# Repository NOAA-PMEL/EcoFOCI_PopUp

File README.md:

# EcoFOCI_PopUp

Under Ice 'Pop-Up' Buoy

################

Legal Disclaimer

This repository is a software product and is not official communication of the National Oceanic and Atmospheric Administration (NOAA), or the United States Department of Commerce (DOC). All NOAA GitHub project code is provided on an 'as is' basis and the user assumes responsibility for its use. Any claims against the DOC or DOC bureaus stemming from the use of this GitHub project will be governed by all applicable Federal law. Any reference to specific commercial products, processes, or services by service mark, trademark, manufacturer, or otherwise, does not constitute or imply their endorsement, recommendation, or favoring by the DOC. The DOC seal and logo, or the seal and logo of a DOC bureau, shall not be used in any manner to imply endorsement of any commercial product or activity by the DOC or the United States Government.

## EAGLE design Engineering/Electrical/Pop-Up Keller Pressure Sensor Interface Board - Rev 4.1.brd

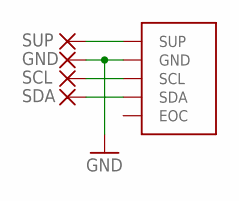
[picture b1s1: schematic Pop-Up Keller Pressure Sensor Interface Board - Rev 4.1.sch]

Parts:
GND: SMD075X015; SMD-0,75X0,15
P1: 4LD; KELLER-4-LD
SCL: SMD075X015; SMD-0,75X0,15
SDA: SMD075X015; SMD-0,75X0,15
SUP: SMD075X015; SMD-0,75X0,15

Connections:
GND: GND.P$1, P1.GND
unnamed: P1.SUP, SUP.P$1
unnamed: P1.SCL, SCL.P$1
unnamed: P1.SDA, SDA.P$1

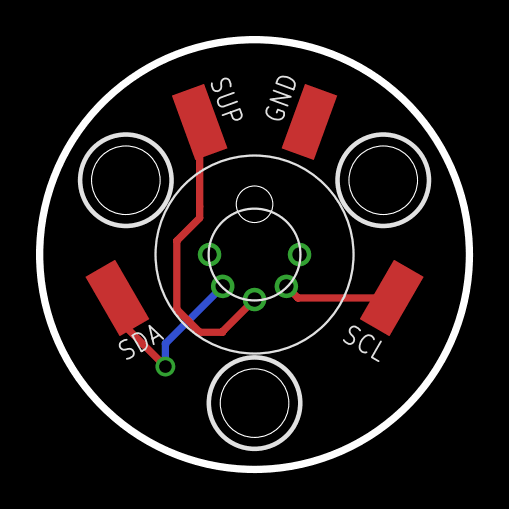
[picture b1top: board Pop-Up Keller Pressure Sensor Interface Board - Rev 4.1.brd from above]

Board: 2 copper layers, 23.9 x 23.9 mm, 5 parts (0 on the bottom side), 4 nets.

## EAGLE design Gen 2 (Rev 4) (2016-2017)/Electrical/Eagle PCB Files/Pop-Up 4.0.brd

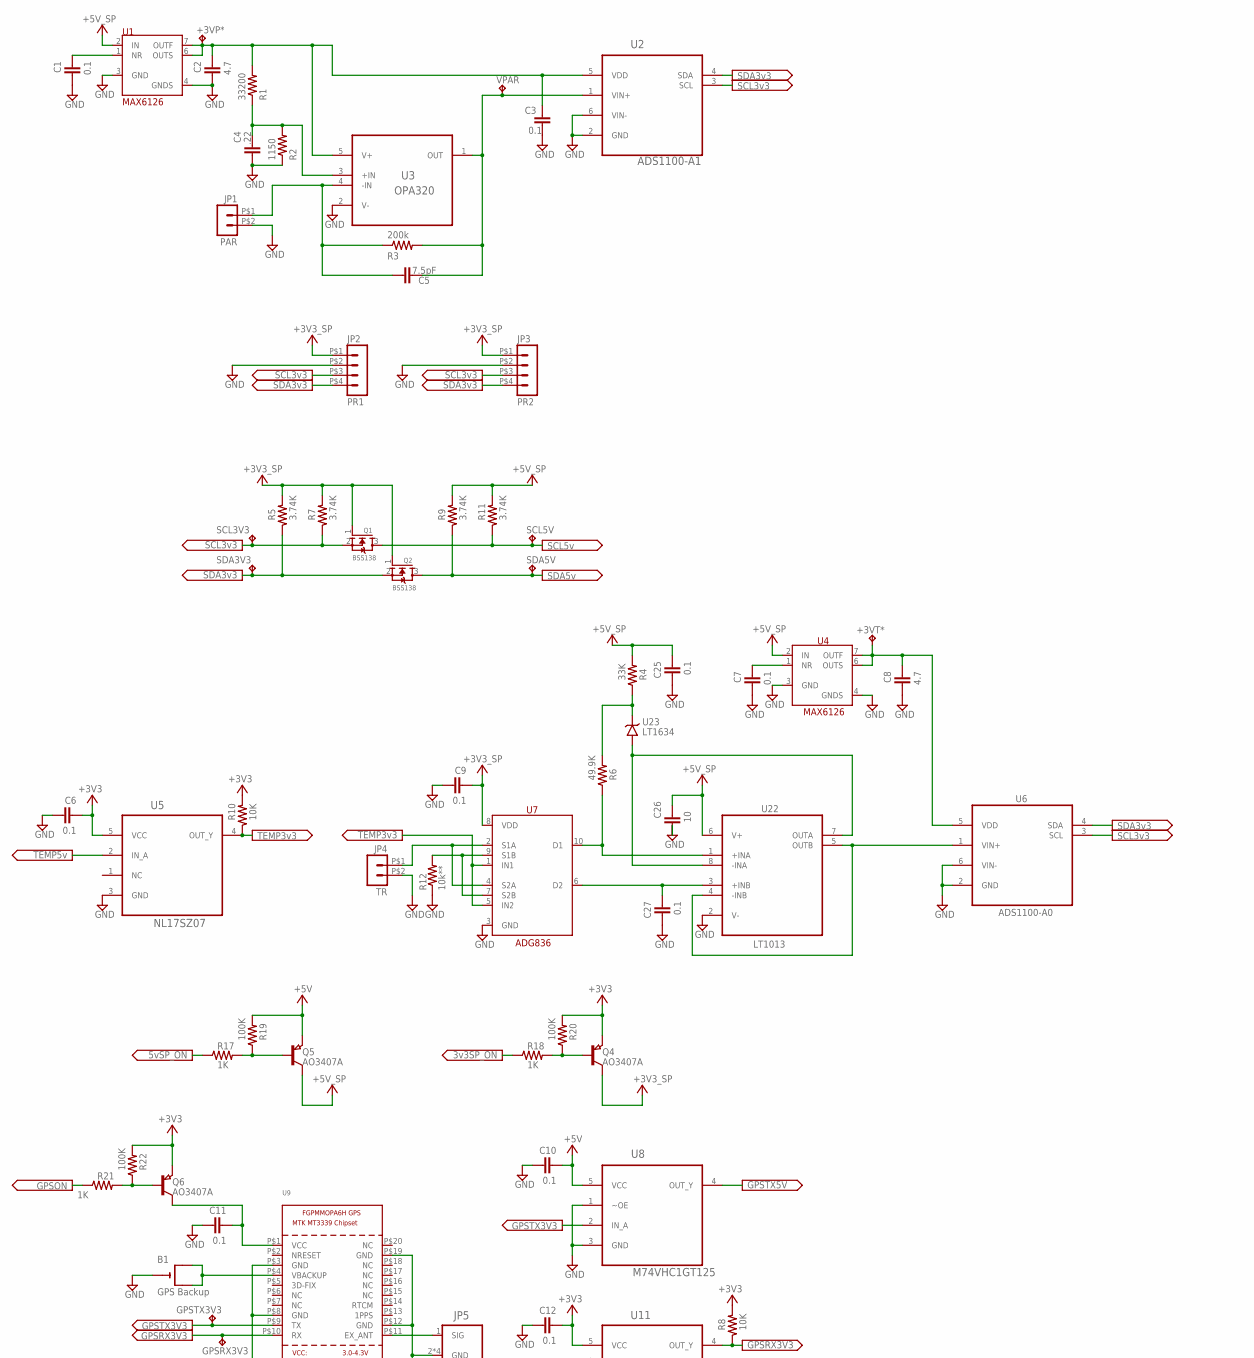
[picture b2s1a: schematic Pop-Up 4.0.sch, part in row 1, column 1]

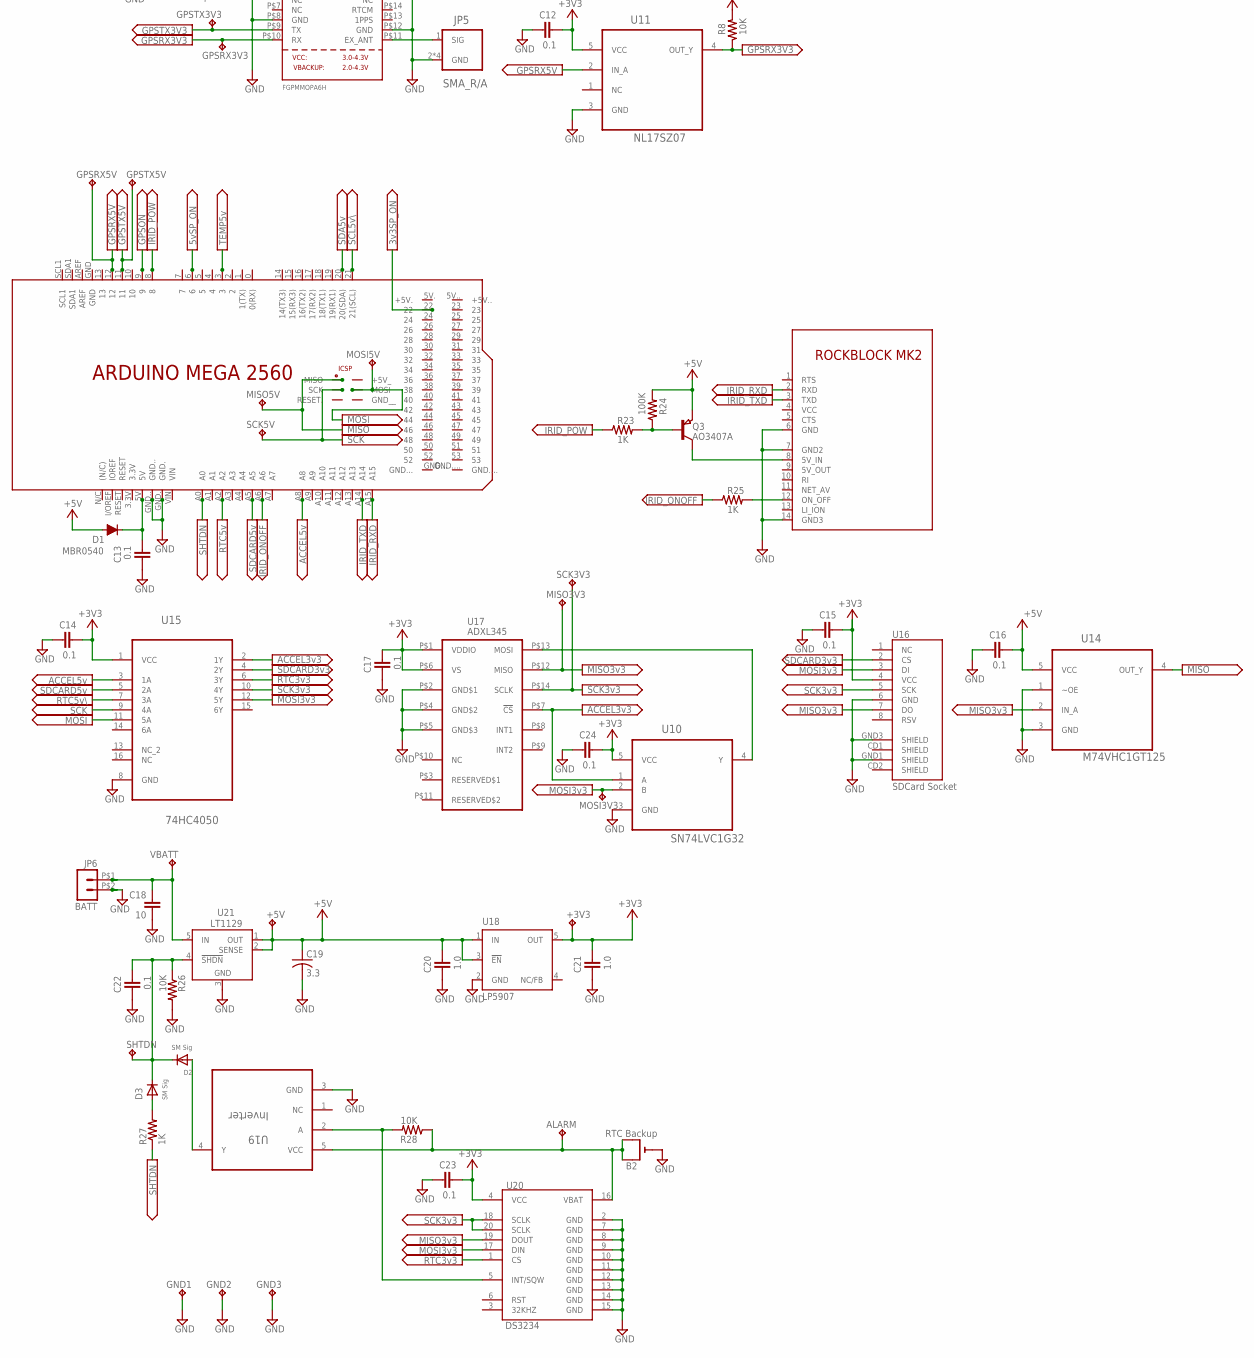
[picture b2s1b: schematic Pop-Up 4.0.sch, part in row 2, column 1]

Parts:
+3V3, +3VP*, +3VT*, +5V: TP-040
ALARM: TP-040
B1: GPS Backup; CR1220-SMD
B2: RTC Backup; CR1220-SMD
C1, C3, C6, C7, C9, C10, C11, C12, C13, C14, C15, C16, C17, C22, C23, C24, C25, C27: 0.1; 0603-CAP; MPN 2222 370 21104
C2, C8: 4.7; 0603-CAP; MPN 2222 370 21104
C4: .22; 0603-CAP; MPN 2222 370 21104
C5: 7.5pF; 0603-CAP; MPN 2222 370 21104
C18: 10; C1206
C19: 3.3; C1206
C20, C21: 1.0; 0603-CAP; MPN 2222 370 21104
C26: 10; C1206; MPN 2222 370 21104
D1: MBR0540; SOD123
D2, D3: SM Sig; SOD-323F
GND1, GND2, GND3: TP-040
GPSRX3V3, GPSRX5V: TP-040
GPSTX3V3, GPSTX5V: TP-040
JP1: PAR; 43650-0215
JP2: PR1; 43650-0415
JP3: PR2; 43650-0415
JP4: TR; 43650-0215
JP5: SMA_R/A; AMPHENOL_901-143
JP6: BATT; 43650-0215
MISO3V3, MISO5V: TP-040
MOSI3V3, MOSI5V: TP-040
Q1, Q2: BSS138; SOT23
Q3, Q4, Q5, Q6: AO3407A; SOT23
R1: 33200; R0603
R2: 1150; R0603
R3: 200k; R0603
R4: 33K; R0603
R5, R7, R9, R11: 3.74K; R0603
R6: 49.9K; R0603
R8, R10, R26, R28: 10K; R0603
R12: 10k**; R1206
R17, R18, R21, R23, R25, R27: 1K; R0603
R19, R20, R22, R24: 100K; R0603
SCK3V3, SCK5V: TP-040
SCL3V3, SCL5V: TP-040
SDA3V3, SDA5V: TP-040
SHTDN: TP-040
U1, U4: MAX6126; SOIC127P600X175-8N
U2: ADS1100-A1; SOT95P280X145-6N
U3: OPA320; SOT95P280X145-5N
U5, U11: NL17SZ07; SOT65P210X110-5N
U6: ADS1100-A0; SOT95P280X145-6N
U7: ADG836; MSOP10
U8, U14: M74VHC1GT125; SOT65P210X110-5N
U9: FGPMMOPA6H
U10: SN74LVC1G32; SOT65P210X110-5N
U12: MEGA2650_UPSIDEDOWNMOUNT
U13: ROCKBLOCK_MK2_UPSIDEDOWN
U15: 74HC4050; SOIC127P600X175-16N
U16: SDCard Socket; MICRO-SD-SOCKET-PP
U17: ADXL345; LGA14
U18: LP5907; SOT23-DBV
U19: Inverter; SOT95P280X145-5N
U20: DS3234
U21: LT1129; Q5-DD
U22: LT1013; SOIC127P600X175-8N
U23: LT1634; S8
VBATT: TP-040
VPAR: TP-040

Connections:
3V3SP_ON: R18.1, U12.22
5VSP_ON: R17.1, U12.6
+3V3: +3V3.1, C6.1, C12.1, C14.1, C15.1, C17.1, C21.1, C23.1, C24.1, Q4.2 (E), Q6.2 (E), R8.2, R10.2, R20.2, R22.2, U5.5 (VCC), U10.5 (VCC), U11.5 (VCC), U15.1 (VCC), U16.4 (VCC), U17.P$1 (VDDIO), U17.P$6 (VS), U18.5 (OUT), U20.4 (VCC)
+3V3SP: C9.1, JP2.P$1 (1), JP3.P$1 (1), Q1.1 (G), Q2.1 (G), Q4.3 (C), R5.2, R7.2, U7.8 (VDD)
+5V: +5V.1, C10.1, C16.1, C19.1, C20.1, C25.1, C26.1, D1.2 (A), Q3.2 (E), Q5.2 (E), R4.2, R19.2, R24.2, U8.5 (VCC), U14.5 (VCC), U18.1 (IN), U18.3 (!EN), U21.1 (OUT), U21.2 (SENSE), U22.6 (V+)
+5V_SP: Q5.3 (C), R9.2, R11.2, U1.2 (IN), U4.2 (IN)
ACCEL3V3: U10.1 (A), U15.2 (1Y), U17.P$7 (!CS)
ACCEL5V: U12.A8, U15.3 (1A)
GND: B1.-, B2.-, C1.2, C2.2, C3.1, C4.2, C6.2, C7.2, C8.2, C9.2, C10.2, C11.2, C12.2, C13.2, C14.2, C15.2, C16.2, C17.2, C18.2, C19.2, C20.2, C21.2, C22.2, C23.2, C24.2, C25.2, C26.2, C27.2, GND1.1, GND2.1, GND3.1, JP1.P$2 (2), JP2.P$2 (2), JP3.P$2 (2), JP4.P$2 (2), JP5.2 (GND), JP5.3 (GND), JP5.4 (GND), JP5.5 (GND), JP6.P$2 (2), R2.1, R12.1, R26.2, U1.3 (GND), U1.4 (GNDS), U2.2 (GND), U2.6 (VIN-), U3.2 (V-), U4.3 (GND), U4.4 (GNDS), U5.3 (GND), U6.2 (GND), U6.6 (VIN-), U7.3 (GND), U8.1 (~OE), U8.3 (GND), U9.P$3 (GND), U9.P$8 (GND), U9.P$12 (GND), U9.P$19 (GND), U10.3 (GND), U11.3 (GND), U12.GND., U12.GND.., U13.6 (GND), U13.7 (GND2), U13.14 (GND3), U14.1 (~OE), U14.3 (GND), U15.8 (GND), U16.6 (GND), U16.GND1 (SHIELD), U16.GND3 (SHIELD), U17.P$2 (GND$1), U17.P$4 (GND$2), U17.P$5 (GND$3), U18.2 (GND), U19.3 (GND), U20.2 (GND), U20.7 (GND), U20.8 (GND), U20.9 (GND), U20.10 (GND), U20.11 (GND), U20.12 (GND), U20.13 (GND), U20.14 (GND), U20.15 (GND), U21.3 (GND), U22.2 (V-)
GPSON: R21.1, U12.9
GPSRX3V3: GPSRX3V3.1, R8.1, U9.P$10 (RX), U11.4 (OUT_Y)
GPSRX5V: GPSRX5V.1, U11.2 (IN_A), U12.12
GPSTX3V3: GPSTX3V3.1, U8.2 (IN_A), U9.P$9 (TX)
GPSTX5V: GPSTX5V.1, U8.4 (OUT_Y), U12.11
IRIDIUMONOFF: R25.1, U12.A6
IRIDIUMPOWER: R23.1, U12.8
IRIDIUMRXD: U12.A15, U13.2 (RXD)
IRIDIUMTXD: U12.A14, U13.3 (TXD)
MISO: MISO5V.1, U12.MISO, U14.4 (OUT_Y)
MISO3V3: MISO3V3.1, U14.2 (IN_A), U16.7 (DO), U17.P$12 (MISO), U20.19 (DOUT)
MOSI: MOSI5V.1, U12.MOSI, U15.11 (5A)
MOSI3V3: MOSI3V3.1, U10.2 (B), U15.12 (5Y), U16.3 (DI), U20.17 (DIN)
unnamed: D2.A, U19.4 (Y)
unnamed: Q3.1 (B), R23.2, R24.1
unnamed: ALARM.1, B2.+$1 (+), B2.+$2 (+1), R28.1, U19.5 (VCC), U20.16 (VBAT)
unnamed: R25.2, U13.12 (ON_OFF)
unnamed: C7.1, U4.1 (NR)
unnamed: C13.1, D1.1 (C), U12.5V
unnamed: JP4.P$1 (1), U7.2 (S1A), U7.4 (S2A)
unnamed: C27.1, U7.6 (D2), U22.3 (+INB)
unnamed: Q3.3 (C), U13.8 (5V_IN)
unnamed: JP5.1 (SIG), U9.P$11 (EX_ANT)
unnamed: +3VT*.1, C8.1, U4.6 (OUTS), U4.7 (OUTF), U6.5 (VDD)
unnamed: R4.1, R6.2, U23.6 (VOUT)
unnamed: U22.7 (OUTA), U22.8 (-INA), U23.4 (GND)
unnamed: B1.+$1 (+), B1.+$2 (+1), U9.P$4 (VBACKUP)
unnamed: Q6.1 (B), R21.2, R22.1
unnamed: R28.2, U19.2 (A), U20.5 (INT/SQW)
unnamed: U6.1 (VIN+), U22.4 (-INB), U22.5 (OUTB)
unnamed: C11.1, Q6.3 (C), U9.P$1 (VCC)
unnamed: +3VP*.1, C2.1, C3.2, R1.2, U1.6 (OUTS), U1.7 (OUTF), U2.5 (VDD), U3.5 (V+)
unnamed: C1.1, U1.1 (NR)
unnamed: C5.2, R3.2, U2.1 (VIN+), U3.1 (OUT), VPAR.1
unnamed: R12.2, U7.7 (S2B), U7.9 (S1B)
unnamed: C4.1, R1.1, R2.2, U3.3 (+IN)
unnamed: C5.1, JP1.P$1 (1), R3.1, U3.4 (-IN)
unnamed: C22.1, D2.C, D3.C, R26.1, SHTDN.1, U21.4 (!SHDN)
unnamed: Q5.1 (B), R17.2, R19.1
unnamed: Q4.1 (B), R18.2, R20.1
unnamed: U10.4 (Y), U17.P$13 (MOSI)
unnamed: R6.1, U7.10 (D1), U22.1 (+INA)
unnamed: D3.A, R27.2
RTC3V3: U15.6 (3Y), U20.1 (CS)
RTC5V: U12.A2, U15.7 (3A)
SCK: SCK5V.1, U12.SCK, U15.9 (4A)
SCK3V3: SCK3V3.1, U15.10 (4Y), U16.5 (SCK), U17.P$14 (SCLK), U20.18 (SCLK), U20.20 (SCLK)
SCL3V3: JP2.P$3 (3), JP3.P$3 (3), Q1.2 (S), R7.1, SCL3V3.1, U2.3 (SCL), U6.3 (SCL)
SCL5V: Q1.3 (D), R11.1, SCL5V.1, U12.21 (21(SCL))
SDA3V3: JP2.P$4 (4), JP3.P$4 (4), Q2.2 (S), R5.1, SDA3V3.1, U2.4 (SDA), U6.4 (SDA)
SDA5V: Q2.3 (D), R9.1, SDA5V.1, U12.20 (20(SDA))
SDCARD3V3: U15.4 (2Y), U16.2 (CS)
SDCARD5V: U12.A5, U15.5 (2A)
SHTDN: R27.1, U12.A0
TEMP3V3: R10.1, U5.4 (OUT_Y), U7.1 (IN1), U7.5 (IN2)
TEMP5V: U5.2 (IN_A), U12.3
VBATT: C18.1, JP6.P$1 (1), U21.5 (IN), VBATT.1

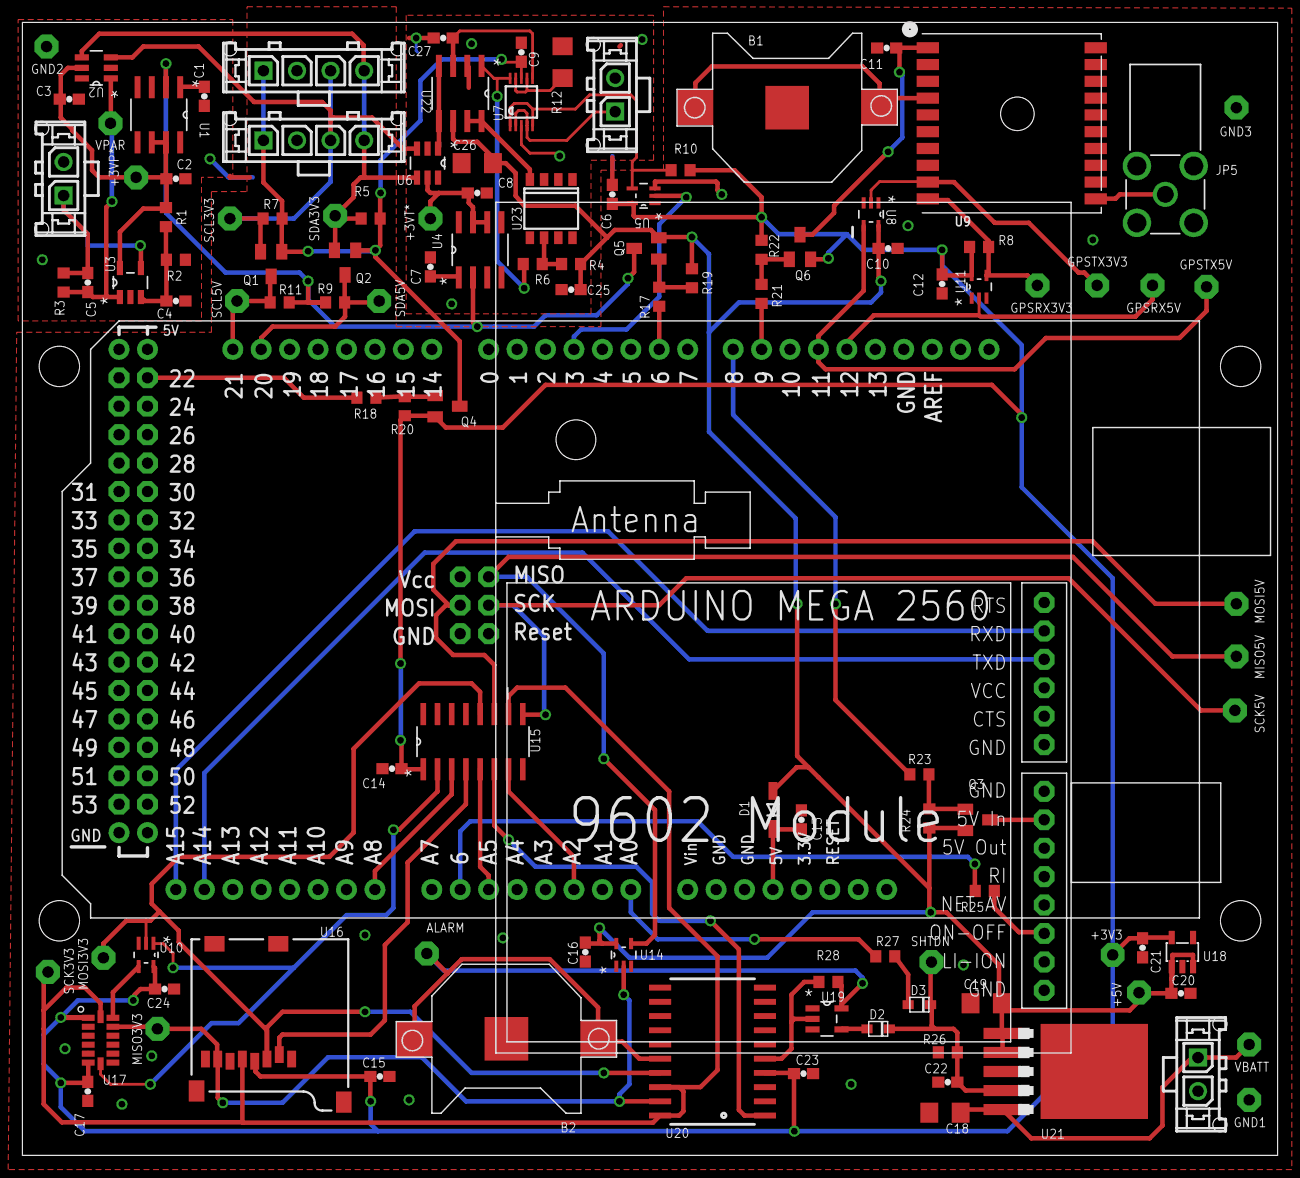
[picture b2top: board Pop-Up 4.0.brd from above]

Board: 2 copper layers, 112.1 x 101.2 mm, 116 parts (0 on the bottom side), 66 nets.

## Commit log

2018-12-13 Rename prototype201_test1_07Dec18_deploymentdialog.txt to testing winter 2018-2019/prototype201_test1_07Dec18_deploymentdialog.txt
2018-12-13 Rename testing winter 2018-2019/prototype201_test1_07Dec18_deploymentdialog.txt to testing winter 2018-2019/deployment dialogs/prototype201_test1_07Dec18_deploymentdialog.txt
2019-03-05 Initial Commit.
    File is reformatted to include all surface data from Pop Ups 003, 004, 005 & 006 deployed in Fall of 2017 and data recovered in Spring of 2018.
2019-07-05 Add data and jupyter analysis scripts
2019-07-05 update July 5 2019
    - 300434063823800
    - 300434063921240
2019-07-08 July 8 2019 Data Update
2019-07-08 July 8 2019 Data update 2
2019-07-09 July 9 2019 Update and new ID
    # 2018 - 300434063823800 - C10/C11 Popup 102 : Active
    # 2018 - 300434063921240 - C2 Popup 101 : Active
    # 2018 - 300434063928220 - Popup 103 : Active **NEW**
2019-07-09 July 9 2019 Update 2
    reprocessing of clocks
2019-07-11 remove holoviews
2019-07-11 July 10 2019 Update
2019-07-11 Update PopupBuoy_Translater.ipynb
    remove more holoviews references
2019-07-16 July 16 2019 Update
2019-07-17 update imei location output for erddap usage
2019-07-31 July 31 2019 Update
2019-08-02 Aug 2 2019 Popup update
2019-08-15 Aug 15 2019 Update
2019-10-23 create Archive folder
    This is for archival documentation on past generations of the pop-up project
2019-10-26 remove data from archive and place in ecoraid
2019-11-04 path update
2020-03-27 Function to Arduino Setup Code
    Temperature Response Test Function added to Arduino Setup Code, now SetupAndSensorCheck_v2
2020-03-30 setup sensor check notes edit
    small edits to comments and instructions in the code
2020-03-30 deleted
2020-04-01 Document renamed without changes
2021-07-13 Notebook processing update
    - fixes calendar issues with datetime in plots
2021-08-16 Archive original repo, add working folders
    moved prior file organization into archive. Current file organization has data processing files under "Data". All data processing scripts in Jupyter notebook have relative paths and use os.path.join 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
2021-08-16 Add in Data folder, error committing last time
    Data folder was previously saved as repo on private account, integrated into EcoFOCI_PopUp repo and deleted private repo .git
2021-08-17 remove gitignore
    remove gitignore so that photos from camera output in Data are included in repo
2021-08-19 Add Background and Instruction Jupyter Notebooks
    Cleaned up a few files, added instruction files
2021-08-24 Added yaml files
    Added yaml files
2021-08-24 add .yaml files
    add .yaml files to data>yaml , re-run temp cal coeff.
2021-08-25 temperature conversion log10 added back
    version == 1 added log10 back to Translator script
2021-08-30 Revert "Master"
2021-08-30 Untrack Data
    untrack raw data (sbd messages are available internally)
    untrack output results data (this shouldn't be freely available here) - work with S.Bell to make data available via ERDDAP
2021-09-09 Update 03_PopUpFloat_Translater.ipynb
    TempConversion method already had logic for an alternative cal bath equation (log10 vs log) but it had not been implemented in the function calls throughout the code. add this to routines and set to 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
2021-09-20 2021 Post Popup processing
    - added transmitting 2020/2021 popups
    - added ability to process multiple id's at once
    - pointed to absolute path instead of local path
    - fixed plotting time labels
2021-09-29 Small modifications/corrections to code
    watch for local path reference though
2022-02-14 Create 03_PopUpFloat_Translater_19bs8apoptop.ipynb
    - this unit used the temperature calculation - version=1 and is unique enough to have its own record
2022-03-30 SD card data for unit 300434063863350
    SD card data for unit 300434063863350
2022-10-21 Pressure Calibration Variation on these units
    - they all need to be multipled by 3 as they have a non-standard 30Bar sensor on them
    - if this happens in future, update code for variable sensors
2023-03-03 Update 03_PopUpFloat_Translater.ipynb
    correct temperature version code

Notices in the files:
parts and their libraries:
User-Submitted: Licensing: Creative Commons ShareAlike 4.0 International - https://creativecommons.org/licenses/by-sa/4.0
